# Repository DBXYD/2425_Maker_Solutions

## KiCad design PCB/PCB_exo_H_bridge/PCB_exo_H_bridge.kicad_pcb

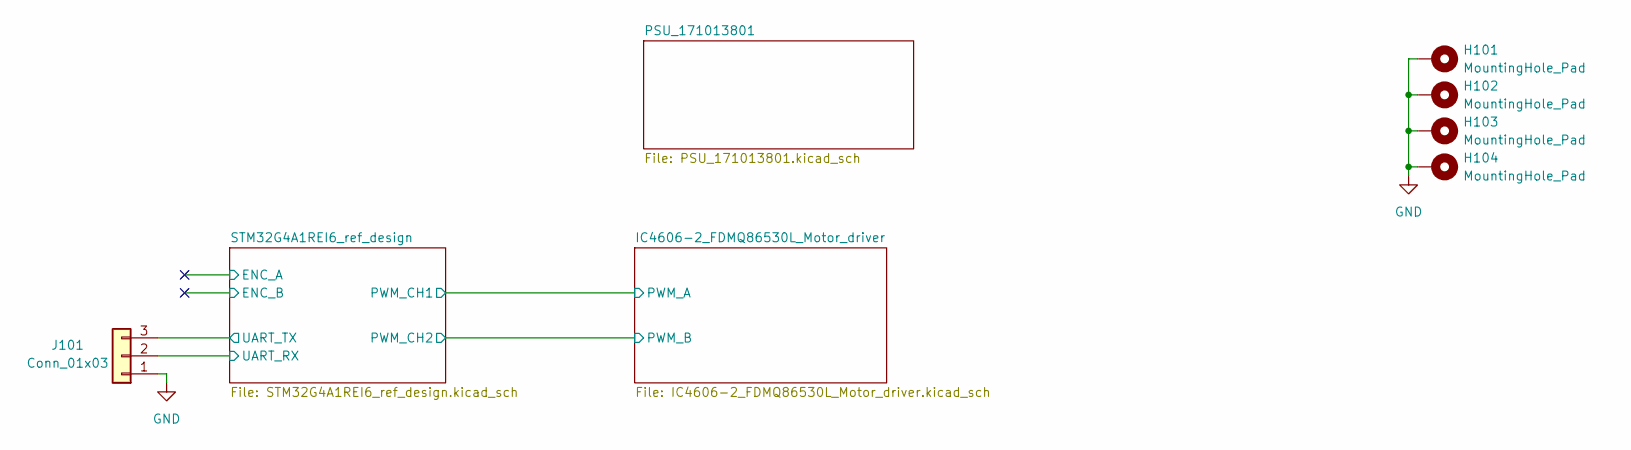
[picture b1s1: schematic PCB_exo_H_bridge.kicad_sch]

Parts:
H101, H102, H103, H104: MountingHole_Pad; MountingHole_2.7mm_M2.5_Pad_Via
J101: Conn_01x03; JST_EH_B3B-EH-A_1x03_P2.50mm_Vertical

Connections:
/STM32G4A1REI6_ref_design/UART_RX: J101.2; also elsewhere on the board
/STM32G4A1REI6_ref_design/UART_TX: J101.3; also elsewhere on the board
GND: H101.1, H102.1, H103.1, H104.1, J101.1; also elsewhere on the board

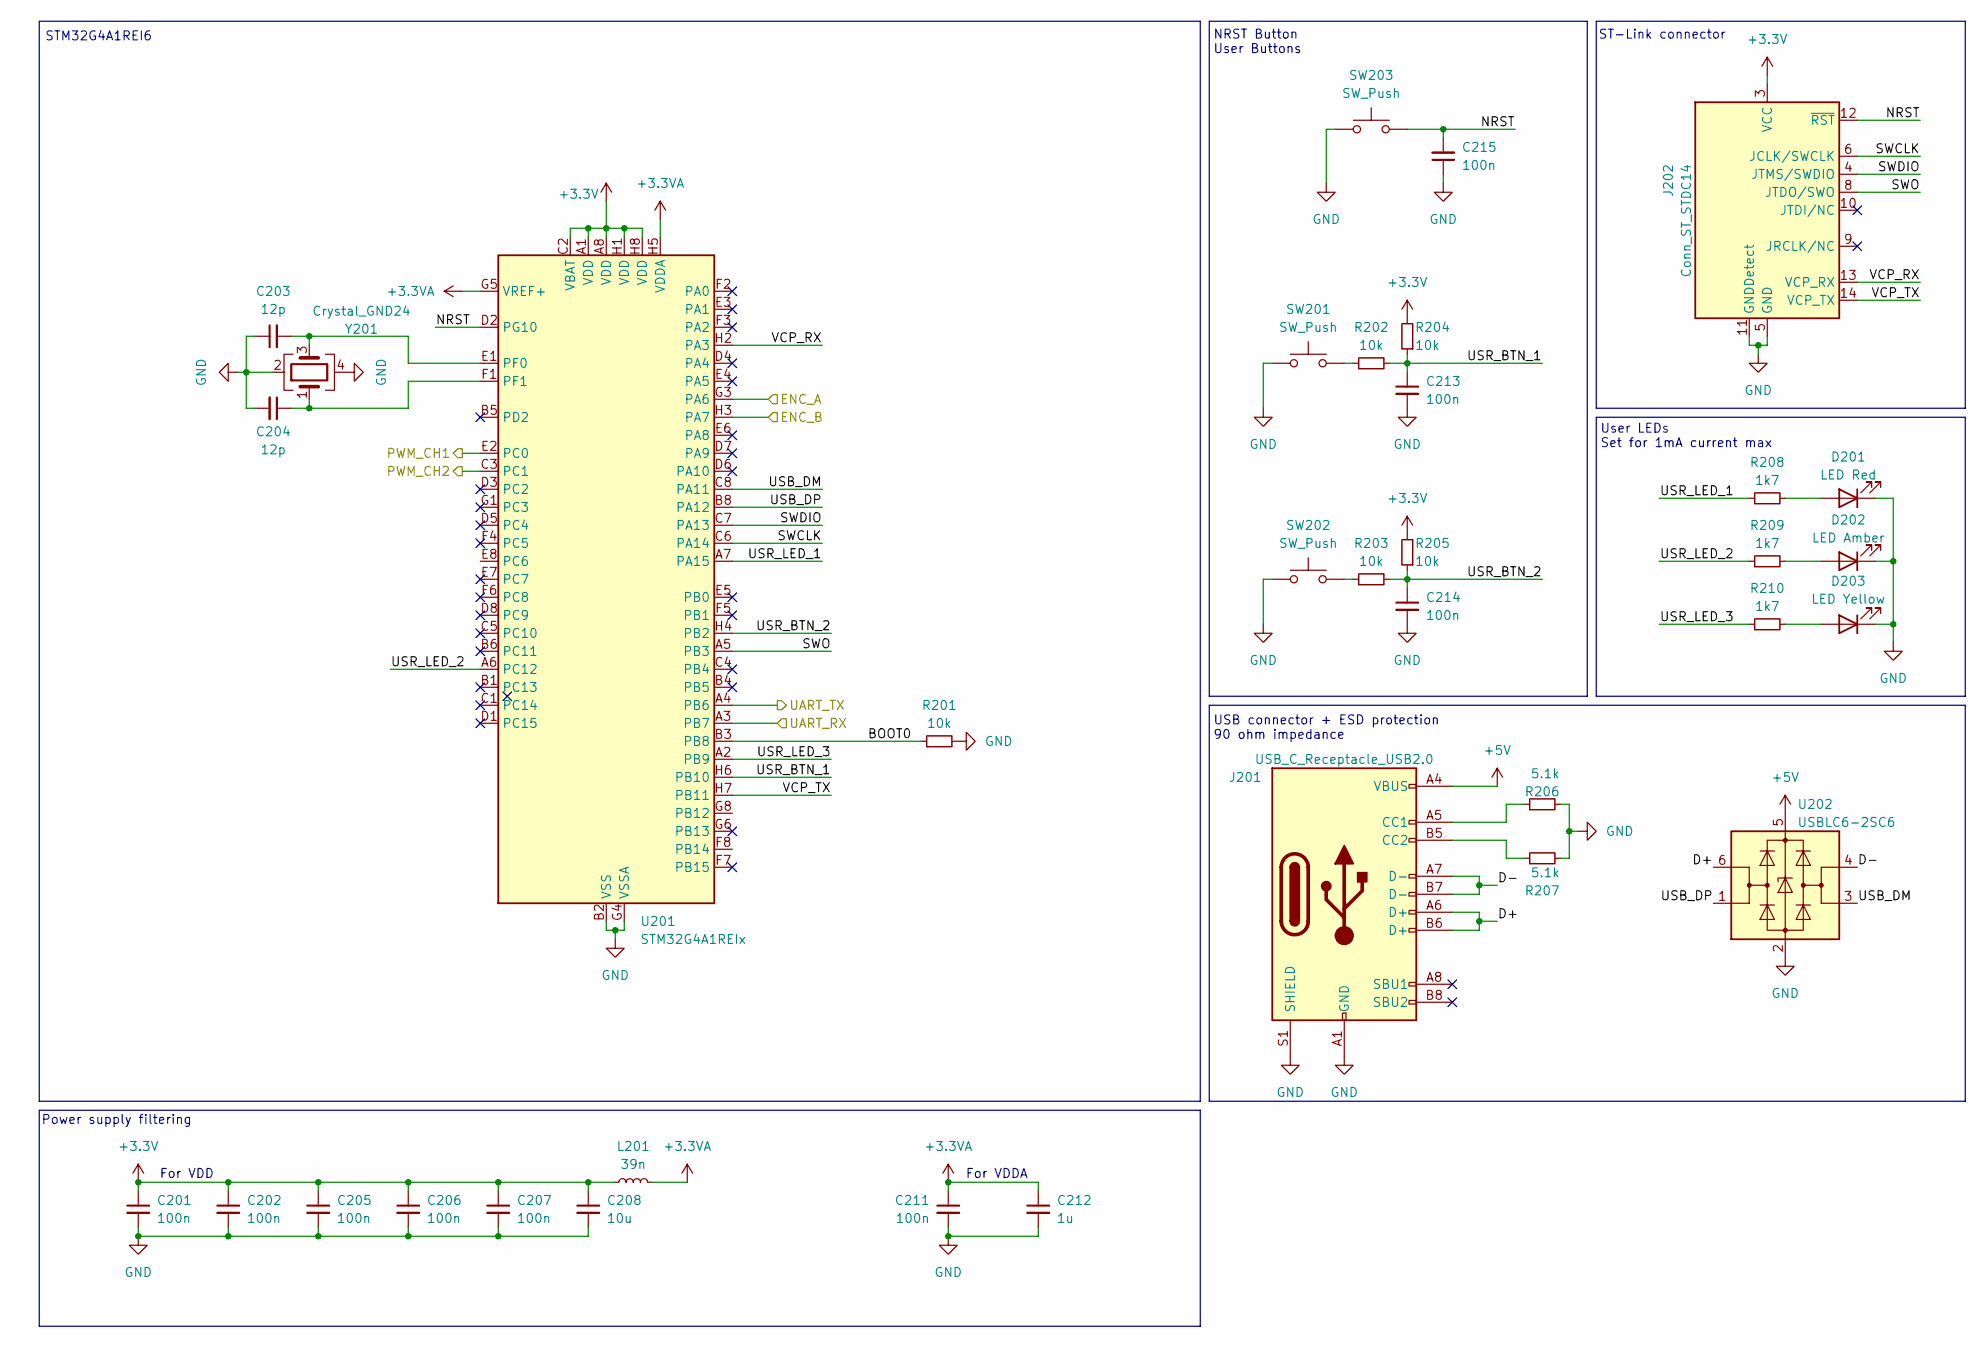
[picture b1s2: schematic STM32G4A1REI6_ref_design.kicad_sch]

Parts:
C201, C202, C205, C206, C207, C211, C213, C214, C215: 100n; C_0402_1005Metric
C203, C204: 12p; C_0402_1005Metric
C208: 10u; C_0603_1608Metric; MPN 885012105020
C212: 1u; C_0603_1608Metric; MPN 885012105006
D201: LED Red; LED_0603_1608Metric; MPN 150060RS55040
D202: LED Amber; LED_0603_1608Metric; MPN 150060AS55040
D203: LED Yellow; LED_0603_1608Metric; MPN 150060YS55040
J201: USB_C_Receptacle_USB2.0; USB_C_Receptacle_HRO_TYPE-C-31-M-12
J202: Conn_ST_STDC14; PinHeader_2x07_P1.27mm_Vertical_SMD
L201: 39n; L_0805_2012Metric
R201, R202, R203, R204, R205: 10k; R_0402_1005Metric
R206, R207: 5.1k; R_0402_1005Metric
R208, R209, R210: 1k7; R_0402_1005Metric
SW201, SW202, SW203: SW_Push; SW_Push_1P1T_NO_CK_KSC6xxJ
U201: STM32G4A1REIx; UFBGA-64_5x5mm_Layout8x8_P0.5mm
U202: USBLC6-2SC6; SOT-23-6
Y201: Crystal_GND24; Crystal_SMD_3225-4Pin_3.2x2.5mm; MPN MCSJK-7U-16.00-10-30-80-B-30

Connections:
+3.3V: C201.1, C202.1, C205.1, C206.1, C207.1, C208.1, J202.3 (VCC), L201.1, R204.2, R205.2, U201.A1 (VDD), U201.A8 (VDD), U201.C2 (VBAT), U201.H1 (VDD), U201.H8 (VDD); also elsewhere on the board
+3.3VA: C211.1, C212.1, L201.2, U201.G5 (VREF+), U201.H5 (VDDA)
+5V: J201.A4 (VBUS), J201.A9 (VBUS), J201.B4 (VBUS), J201.B9 (VBUS), U202.5 (VBUS)
/IC4606-2_FDMQ86530L_Motor_driver/PWM_A: U201.E2 (PC0); also elsewhere on the board
/IC4606-2_FDMQ86530L_Motor_driver/PWM_B: U201.C3 (PC1); also elsewhere on the board
/STM32G4A1REI6_ref_design/BOOT0: R201.1, U201.B3 (PB8)
/STM32G4A1REI6_ref_design/D+: J201.A6 (D+), J201.B6 (D+), U202.6 (I/O1)
/STM32G4A1REI6_ref_design/D-: J201.A7 (D-), J201.B7 (D-), U202.4 (I/O2)
/STM32G4A1REI6_ref_design/ENC_A: U201.G3 (PA6)
/STM32G4A1REI6_ref_design/ENC_B: U201.H3 (PA7)
/STM32G4A1REI6_ref_design/NRST: C215.2, J202.12 (~RST), SW203.2, U201.D2 (PG10)
/STM32G4A1REI6_ref_design/SWCLK: J202.6 (JCLK/SWCLK), U201.C6 (PA14)
/STM32G4A1REI6_ref_design/SWDIO: J202.4 (JTMS/SWDIO), U201.C7 (PA13)
/STM32G4A1REI6_ref_design/SWO: J202.8 (JTDO/SWO), U201.A5 (PB3)
/STM32G4A1REI6_ref_design/UART_RX: U201.A3 (PB7); also elsewhere on the board
/STM32G4A1REI6_ref_design/UART_TX: U201.A4 (PB6); also elsewhere on the board
/STM32G4A1REI6_ref_design/USB_DM: U201.C8 (PA11), U202.3 (I/O2)
/STM32G4A1REI6_ref_design/USB_DP: U201.B8 (PA12), U202.1 (I/O1)
/STM32G4A1REI6_ref_design/USR_BTN_1: C213.1, R202.2, R204.1, U201.H6 (PB10)
/STM32G4A1REI6_ref_design/USR_BTN_2: C214.1, R203.2, R205.1, U201.H4 (PB2)
/STM32G4A1REI6_ref_design/USR_LED_1: R208.1, U201.A7 (PA15)
/STM32G4A1REI6_ref_design/USR_LED_2: R209.1, U201.A6 (PC12)
/STM32G4A1REI6_ref_design/USR_LED_3: R210.1, U201.A2 (PB9)
/STM32G4A1REI6_ref_design/VCP_RX: J202.13 (VCP_RX), U201.H2 (PA3)
/STM32G4A1REI6_ref_design/VCP_TX: J202.14 (VCP_TX), U201.H7 (PB11)
GND: C201.2, C202.2, C203.1, C204.2, C205.2, C206.2, C207.2, C208.2, C211.2, C212.2, C213.2, C214.2, C215.1, D201.1 (K), D202.1 (K), D203.1 (K), J201.A1 (GND), J201.A12 (GND), J201.B1 (GND), J201.B12 (GND), J201.S1 (SHIELD), J202.5 (GND), J202.7 (GND), J202.11 (GNDDetect), R201.2, R206.2, R207.2, SW201.1, SW202.1, SW203.1, U201.B2 (VSS), U201.B7 (VSS), U201.G2 (VSS), U201.G4 (VSSA), U201.G7 (VSS), U202.2 (GND), Y201.2, Y201.4; also elsewhere on the board
unnamed: D201.2 (A), R208.2
unnamed: D202.2 (A), R209.2
unnamed: D203.2 (A), R210.2
unnamed: J201.A5 (CC1), R206.1
unnamed: J201.B5 (CC2), R207.1
unnamed: R202.1, SW201.2
unnamed: R203.1, SW202.2
unnamed: C203.2, U201.E1 (PF0), Y201.3
unnamed: C204.1, U201.F1, Y201.1

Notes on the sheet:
NRST Button User Buttons
STM32G4A1REI6
User LEDs Set for 1mA current max
For VDDA
Power supply filtering
USB connector + ESD protection 90 ohm impedance
ST-Link connector
For VDD

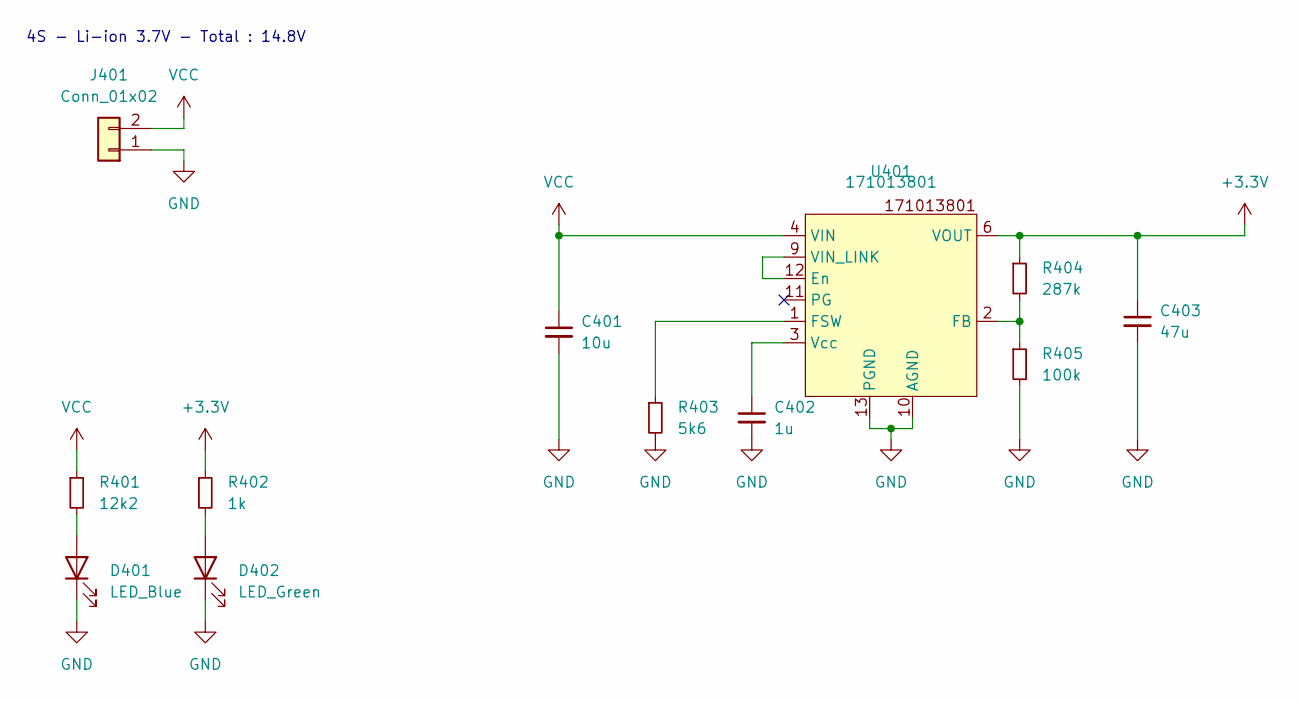
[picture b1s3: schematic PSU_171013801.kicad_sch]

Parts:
C401: 10u; C_0603_1608Metric; MPN 885012106031
C402: 1u; C_0603_1608Metric; MPN 885012206076
C403: 47u; C_0805_2012Metric; MPN 885012107006
D401: LED_Blue; LED_0603_1608Metric
D402: LED_Green; LED_0603_1608Metric
J401: Conn_01x02; AMASS_XT60-F_1x02_P7.20mm_Vertical
R401: 12k2; R_0402_1005Metric
R402: 1k; R_0402_1005Metric
R403: 5k6; R_0402_1005Metric
R404: 287k; R_0402_1005Metric
R405: 100k; R_0402_1005Metric
U401: 171013801; MPN 171013801

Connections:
+3.3V: C403.1, R402.1, R404.1, U401.6 (VOUT), U401.7 (VOUT); also elsewhere on the board
GND: C401.2, C402.2, C403.2, D401.1 (K), D402.1 (K), J401.1, R403.2, R405.2, U401.10 (AGND), U401.13 (PGND); also elsewhere on the board
unnamed: D401.2 (A), R401.2
unnamed: D402.2 (A), R402.2
unnamed: U401.9 (VIN_LINK), U401.12 (En)
unnamed: R404.2, R405.1, U401.2 (FB)
unnamed: R403.1, U401.1 (FSW)
unnamed: C402.1, U401.3 (Vcc)
VCC: C401.1, J401.2, R401.1, U401.4 (VIN), U401.5 (VIN); also elsewhere on the board

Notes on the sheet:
4S - Li-ion 3.7V - Total : 14.8V

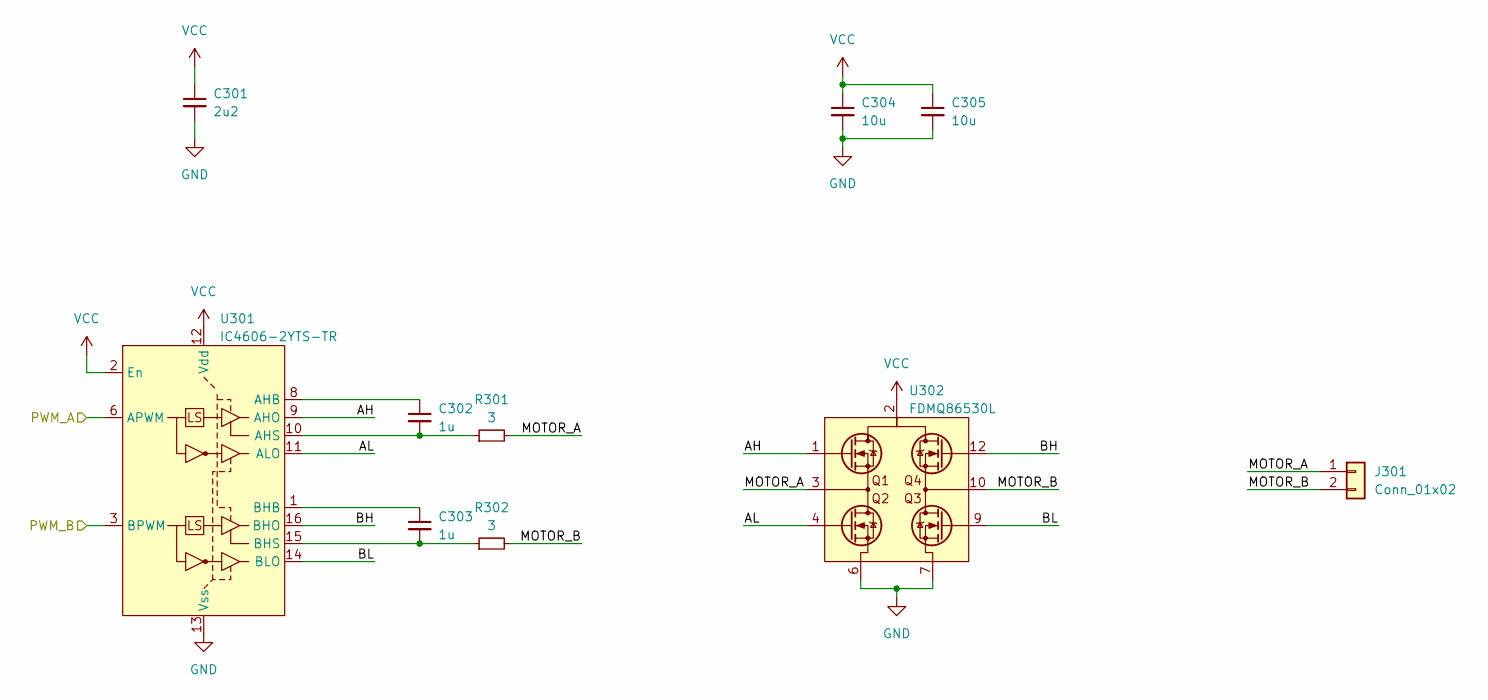
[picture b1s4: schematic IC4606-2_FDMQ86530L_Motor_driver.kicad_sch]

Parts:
C301: 2u2; C_0603_1608Metric; MPN 885012106018
C302, C303: 1u; C_0603_1608Metric; MPN 885012206076
C304, C305: 10u; C_0603_1608Metric; MPN 885012106031
J301: Conn_01x02; PhoenixContact_MSTBA_2,5_2-G-5,08_1x02_P5.08mm_Horizontal
R301, R302: 3; R_0805_2012Metric
U301: IC4606-2YTS-TR; TSSOP-16_4.4x5mm_P0.65mm; MPN IC4606-2YTS-TR
U302: FDMQ86530L

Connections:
/IC4606-2_FDMQ86530L_Motor_driver/AH: U301.9 (AHO), U302.1
/IC4606-2_FDMQ86530L_Motor_driver/AL: U301.11 (ALO), U302.4
/IC4606-2_FDMQ86530L_Motor_driver/BH: U301.16 (BHO), U302.12
/IC4606-2_FDMQ86530L_Motor_driver/BL: U301.14 (BLO), U302.9
/IC4606-2_FDMQ86530L_Motor_driver/MOTOR_A: J301.1, R301.2, U302.3
/IC4606-2_FDMQ86530L_Motor_driver/MOTOR_B: J301.2, R302.2, U302.10
/IC4606-2_FDMQ86530L_Motor_driver/PWM_A: U301.6 (APWM); also elsewhere on the board
/IC4606-2_FDMQ86530L_Motor_driver/PWM_B: U301.3 (BPWM); also elsewhere on the board
GND: C301.2, C304.2, C305.2, U301.13 (Vss), U302.5, U302.6, U302.7, U302.8; also elsewhere on the board
unnamed: C302.1, U301.8 (AHB)
unnamed: C302.2, R301.1, U301.10 (AHS)
unnamed: C303.1, U301.1 (BHB)
unnamed: C303.2, R302.1, U301.15 (BHS)
VCC: C301.1, C304.1, C305.1, U301.2 (En), U301.12 (Vdd), U302.2, U302.11; also elsewhere on the board

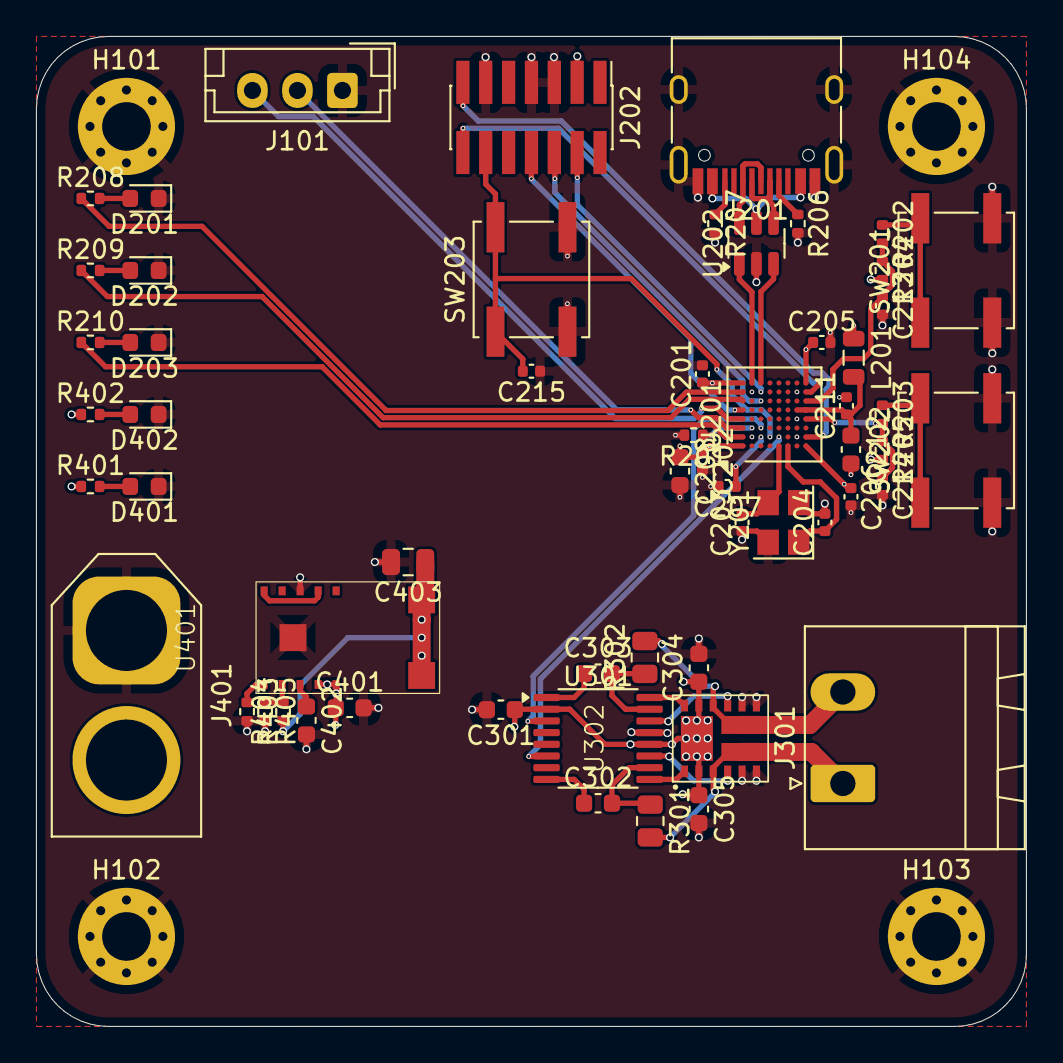
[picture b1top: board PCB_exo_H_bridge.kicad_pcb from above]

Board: 4 copper layers, 55.0 x 55.0 mm, 62 parts (0 on the bottom side), 50 nets.

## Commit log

2025-02-02 starting pcb solution
2025-02-02 exo done
